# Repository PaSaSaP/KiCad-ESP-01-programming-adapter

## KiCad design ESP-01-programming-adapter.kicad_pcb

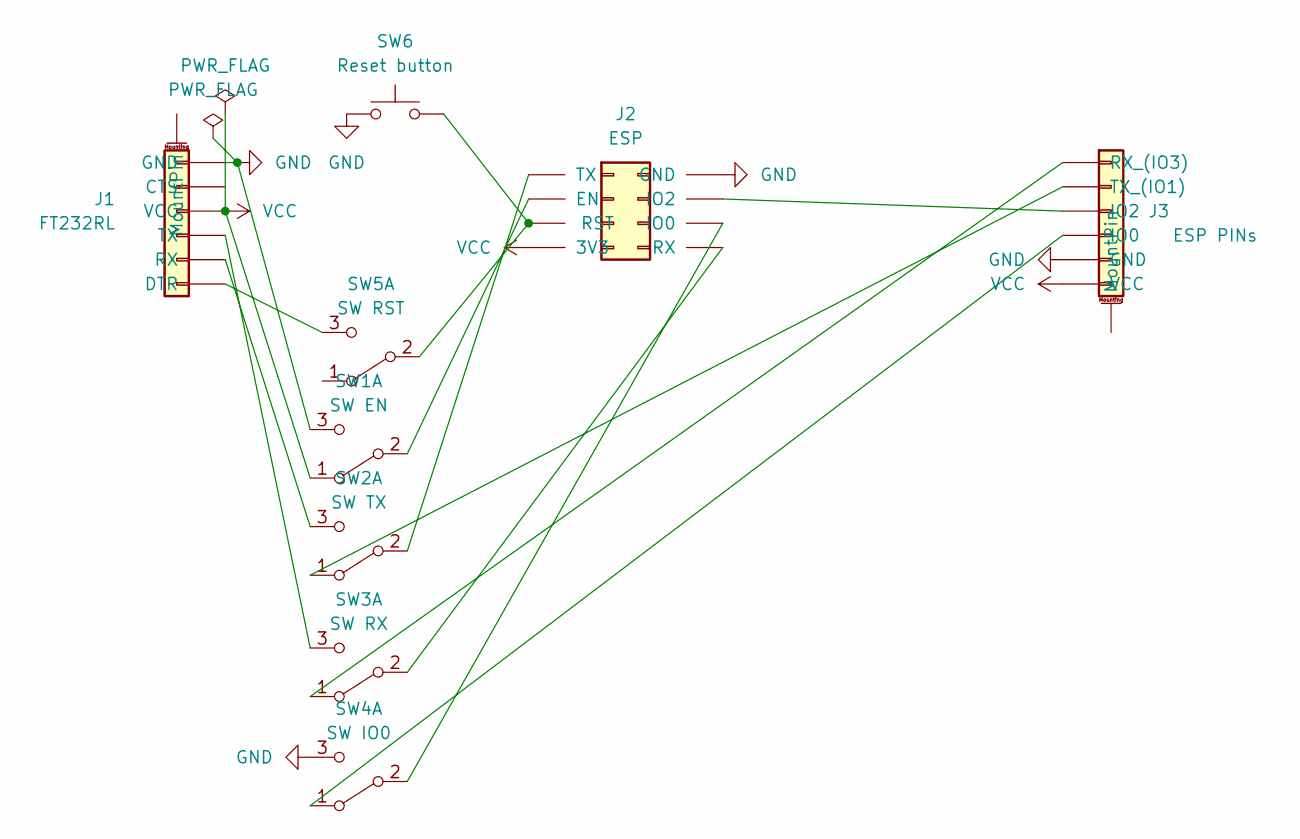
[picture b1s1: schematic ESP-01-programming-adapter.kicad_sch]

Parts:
J1: FT232RL; PinHeader_1x07_P2.54mm_Horizontal
J2: ESP; PinSocket_2x04_P2.54mm_Vertical
J3: ESP PINs; PinHeader_1x07_P2.54mm_Horizontal
SW1: SW EN; PinHeader_1x03_P2.54mm_Vertical
SW2: SW TX; PinHeader_1x03_P2.54mm_Vertical
SW3: SW RX; PinHeader_1x03_P2.54mm_Vertical
SW4: SW IO0; PinHeader_1x03_P2.54mm_Vertical
SW5: SW RST; PinHeader_1x03_P2.54mm_Vertical
SW6: Reset button; FanPinHeader_1x03_P2.54mm_Vertical

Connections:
GND: J1.6 (GND), J2.8 (GND), J3.5 (GND), SW1.3 (C), SW4.3 (C), SW6.1
unnamed: J1.1 (DTR), SW5.3 (C)
unnamed: J1.2 (RX), SW2.3 (C)
unnamed: J1.3 (TX), SW3.3 (C)
unnamed: J2.1 (TX), SW2.2 (B)
unnamed: J2.2 (EN), SW1.2 (B)
unnamed: J2.3 (RST), SW5.2 (B), SW6.2
unnamed: J2.5 (RX), SW3.2 (B)
unnamed: J2.6 (IO0), SW4.2 (B)
unnamed: J2.7 (IO2), J3.3 (IO2)
unnamed: J3.1 (RX_(IO3)), SW3.1 (A)
unnamed: J3.2 (TX_(IO1)), SW2.1 (A)
unnamed: J3.4 (IO0), SW4.1 (A)
VCC: J1.4 (VCC), J2.4 (3V3), J3.6 (VCC), SW1.1 (A)

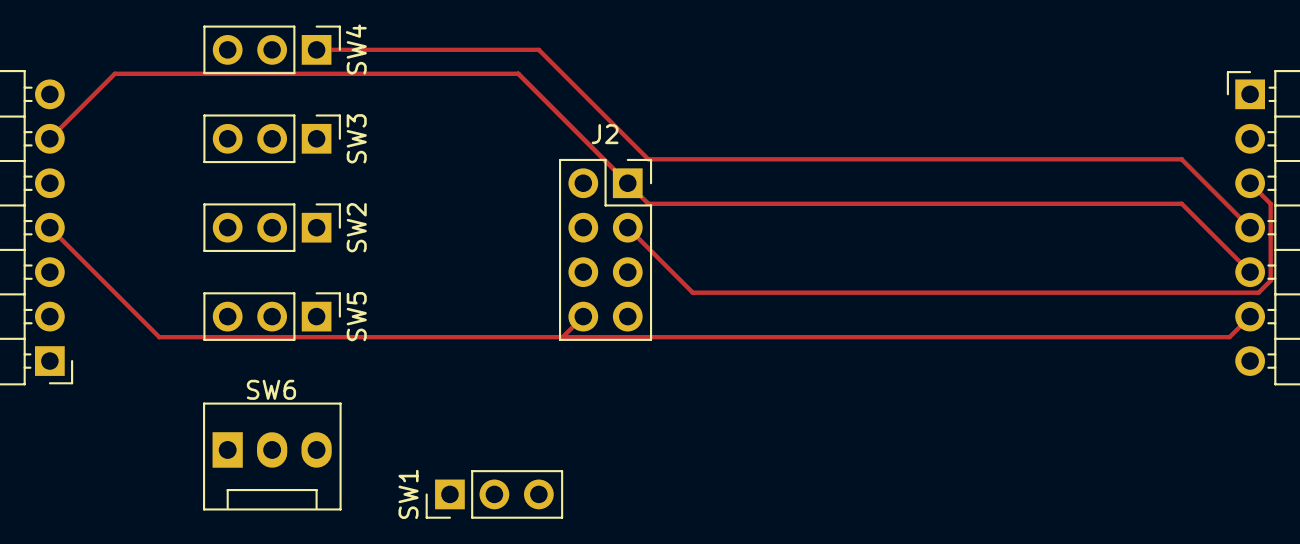
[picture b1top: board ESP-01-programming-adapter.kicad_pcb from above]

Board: 2 copper layers, 9 parts (0 on the bottom side), 14 nets.
